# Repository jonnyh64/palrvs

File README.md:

# Rationale

This work started within the thread
"Project to create an ATX 80286 mainboard based on the IBM 5170"
at the Vintage Computer Federation Forums
(https://forum.vcfed.org/index.php?threads/project-to-create-an-atx-80286-mainboard-based-on-the-ibm-5170.1243108/).

The thread creator (username "rodney") looked for help on how to retrieve the PAL equations
of U87 and U130 on the IBM 5170 (the original IBM PC/AT computer) motherboard.
While I tried to help, he figured the equations out with other tooling from
http://techno-junk.org, but I found the topic interesting, so I kept on researching.

# History

Reverse engineering PAL chips has likely been done as early as in the 1980s, when plenty
of companies cloned the PC/AT. Probably this has just not been publicly documented.

The earliest description of the idea behind I could find was a schematic from 2007 with
title "PLD Analysis Board" developed by Charles M. (I'm trying to avoid publishing full names,
hence "M.") and apparently originally available at http://cgfm2.emuviews.com. This site
is no longer available, but a small subset of the information and schematics can be found at
http://techno-junk.org. A PCB design for these schematics is available at
https://github.com/pascalorama/paldumper.

Another description of the same idea has been published in the Vintage Computer Federation
Forums by user "Chuck(G)" (Blog entries "Cloning a PAL/HAL") in October 2011. He was describing
how to do the brute force readout on a PAL10L8 using a PC parallel port adapter and suggested
to use a microcontroller for more complicated PALs. The microcontroller idea was implemented
and described at https://electrickery.hosting.philpem.me.uk/digaud/arduino/ppread/palread.html.

In 2018, another implementation of the same idea was published at
https://github.com/psurply/ReGAL.

In 2020, https://github.com/DuPAL-PAL-DUmper was published, providing
support for more PALs (even registered ones).

The "Retro Chip Tester Professional" also supports reading protected PALs - see
https://8bit-museum.de/hardware-projekte/hardware-projekte-chip-tester-english/.

Rodney used the "EPROM readout adapter" from http://techno-junk.org which basically
"misuses" a chip programmer to apply all possible input combinations to the PAL via the
EPROM address lines A0..A17. An analysis tool is then used to transform the "EPROM dump"
into boolean equations. However, the boolean simplification and the job to produce a
"fuse map" JEDEC file used to burn the equations into a PAL/GAL device is left to other tools.

# Credits

Thanks go to:
- User "rodney" from the vcfed forums for kicking this all off
- User "Chuck(G)" from the vcfed forums for his excellent write-up on PAL reversing
- Charles M. from http://techno-junk.org for his "EPROM adapter" idea
- User "Eudimorphodon" from the vcfed forums for helping me understand PAL/GAL details

# Restrictions

The adapter and the scripts in this project only support the PAL16L8 chip for reading and
the GAL16V8 chip for writing. From the latter, only the subset of features necessary to use
it for replacing a PAL16L8 is used.

# Idea

The main idea of this project is to provide a "one stop solution" to make a clone
of a PAL16L8 in the form of a GAL16V8. It consists of:
- A KiCad project (including PCB) implementing http://techno-junk.org/files/adapter-v2-cap.png
- A Python script "pete.py" to convert a PAL "EPROM dump" into a truth table and GAL equations
- A Python script "simplegalasm.py" to convert GAL equations into a JED file which can be written into a GAL16V8

For complex PALs, it might be necessary to manually tune the GAL equations generated by "pete.py",
see examples below.

# Usage

## Build the adapter

You need to build up a circuit board according to the following schematic:

It is up to you to either hand wire this on a perfboard or to build it up with the
provided KiCad PCB. If you choose the latter, I have published it for easy ordering
at https://aisler.net/p/IUTCWVJK,
but you also might order it at your preferred PCB manufacturer, of course.

The original schematic from Charles M. suggested 4k7 resistors. This value doesn‘t work
for me (it does not give a stable reading with my minipro chip programmer) and neither
does 2k2. Only after going down to 1k, it worked for me and so you also might need to experiment.

## Install Python

Go to www.python.org, download a recent Python version (anything >= 3.7 should do) and install it.

## Generate "EPROM dump"

Put your PAL16L8 into the adapter and the adapter into your chip programmer.

(Do **NOT** put your PAL16L8 into your chip programmer directly - this will not work.)

Instruct your chip programming application to read a 27C020 EPROM and save the data
to a file, e.g. named pal.bin. The generated file length must be 262144
bytes. If your file length is different, something is broken. Do not try to continue,
it will not work.

E.g., if you own one of the popular MiniPRO TL866xx series of chip programmers and
have the excellent command line application from https://gitlab.com/DavidGriffith/minipro
installed, use:
```
minipro -p am27c020@dip32 -x -r pal.bin
```

**ATTENTION**: I found that this dump does not always work reliably, possibly due to timing
issues. Please make sure to perform the dump multiple times and compare the files. If you
cannot get multiple identical dumps, something is wrong in your setup.

## Generate the equations

On your command line, run `python3 pete.py pal.bin` (adapting the filename
to what you have chosen). This will generate a file called
pal_pete_equations.pld (adapted to your filename), which contains
the PAL equations.

## Fix up the equations

A GAL16V8 (like a PAL16L8) only supports up to 7 products per output value and
only up to 1 product per output enable. For complex PALs where one output value
depends on another output value, pete.py might not be able to find equations
within these limits. In this case, you need to think how to optimize further and
fix up the equations manually.

## Generate the JED file

On your command line, run `python3 simplegalasm.py pal_pete_equations.pld`
(again, adapting the filename to what you have chosen). This will generate a file called
pal.jed.

## Program your GAL

Put your GAL16V8B DIRECTLY into your chip programmer (NOT using the adapter!) and
instruct your EPROM programmer to write pal.jed to the GAL.

Again with the minipro command line utility as example:
```
minipro -p gal16v8b -w pal.jed
```

**ATTENTION**: Be careful to specify the exact GAL type you are using. "gal16v8" and
"gal16v8b" are **NOT** compatible at the chip programming level. The fuse maps (i.e.
the fuse numbers) are the same, but the order in which the fuse information is sent
during chip programming differ (this applies to fuse numbers 2120 to 2193). If
you specify the wrong type, programming seems to work fine, but the GAL outputs
will not behave according to the equations (just think about what happens when
you shuffle fuse numbers 2120 to 2193...).

# Examples

## Example 1

The first example analyzes the equations of U87 on the IBM 5170 (the original
IBM PC/AT computer) motherboard.

First, dump the PAL with the adapter PCB as described above:
```
minipro -p am27c020@dip32 -x -r ibm_5170_u87.bin
```

Then, let pete.py find out the equations:
As the U87 pin names are known from the IBM Personal Computer AT technical reference,
we pass them to pete.py:
```
python3 pete.py -p "RAS,MEMW,IOR,AIOW,Q1,IO_CS_16,AEN_1,AEN_2,Q4,FSYS_16,END_CYC,RES_0WS,DMA_AEN,XA0,XBHE,GATE_245,DIR_245,DATA_CONV" ibm_5170_u87.bin
```

The generated equations in ibm_5170_u87_pete_equations.pld will have one equation
which cannot be translated directly into a GAL fuse map. Let's leave
ibm_5170_u87_pete_equations.pld untouched and create a copy to modify:
```
cp ibm_5170_u87_pete_equations.pld ibm_5170_u87.pld
```

The problematic equation is:
```
XBHE.oe = !AEN_1
  # !AEN_2;
```

GAL16V8s only support one term per output enable. So we need to find a simplification.
Looking around in the remaining file, we will find:
```
!DMA_AEN = !AEN_1
  # !AEN_2;
```

That means, that the pin value equation (which **DOES** support more than one term!) for
`!DMA_AEN` is the same as for `XBHE.oe`. We can therefore replace the equation for `XBHE.oe`
like this:
```
XBHE.oe = !DMA_AEN;
```

Doing this change in ibm_5170_u87.pld gives as equations usable for creating the fuse map:
```
python3 simplegalasm.py ibm_5170_u87.pld
```

Congratulations, you can now program a GAL16V8B for replacing U87 in your IBM 5170 motherboard:
```
minipro -p gal16v8b -w ibm_5170_u87.jed
```

## Example 2

The second example analyzes the other PAL on the IBM 5170 motherboard: U130.

Get the EPROM dump using the adapter PCB:
```
minipro -p am27c020@dip32 -x -r ibm_5170_u130.bin
```

Let pete.py find out the equations:
```
python3 pete.py -p "RESET,ERROR,BUSY,XA0,XA3,XIOW,SM_IO,CS287,INTA,TIEDGND_11,NPCS,UNUSED_13,UNUSED_14,UNUSED_15,UNUSED_16,RESET_287,IRQ_13,BUSY_286" ibm_5170_u130.bin
```

This time, the equation for one output value will not be directly usable, so create a copy to modify again:
```
cp ibm_5170_u130_pete_equations.pld ibm_5170_u130.pld
```

The problematic equation is:
```
!UNUSED_14 = !RESET & XA3
  # !RESET & XIOW
  # !RESET & SM_IO
  # !RESET & CS287
  # !RESET & !INTA
  # ERROR
  # BUSY
  # TIEDGND_11;
```

GAL16V8s only support at most 7 terms per output value. So we need to find a simplification.
Looking around in the remaining file, we will find:
```
!IRQ_13 = ERROR
  # BUSY;
```

So, `ERROR # BUSY` can be replaced by `!IRQ_13`:
```
!UNUSED_14 = !RESET & XA3
  # !RESET & XIOW
  # !RESET & SM_IO
  # !RESET & CS287
  # !RESET & !INTA
  # !IRQ_13
  # TIEDGND_11;
```

Doing this change in ibm_5170_u130.pld gives as equations usable for creating the fuse map:
```
python3 simplegalasm.py ibm_5170_u130.pld
```

Congratulations, you can now program a GAL16V8B for replacing U130 in your IBM 5170 motherboard:
```
minipro -p gal16v8b -w ibm_5170_u130.jed
```

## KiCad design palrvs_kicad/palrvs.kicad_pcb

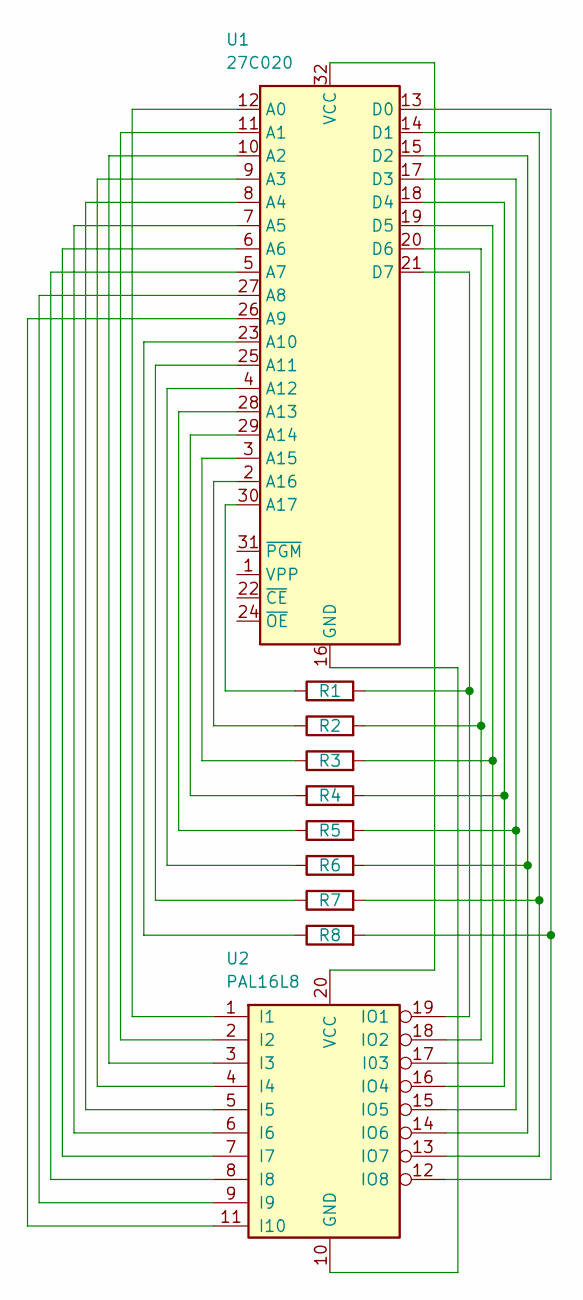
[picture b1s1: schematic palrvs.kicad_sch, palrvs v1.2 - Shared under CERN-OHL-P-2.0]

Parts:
R1, R2, R3, R4, R5, R6, R7, R8: 4k7; R_Axial_DIN0207_L6.3mm_D2.5mm_P7.62mm_Horizontal
U1: 27C020; Mirrored_DIP-32_W15.24mm
U2: PAL16L8; ZIF-20_W7.62mm_Socket

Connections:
unnamed: U1.12 (A0), U2.1 (I1)
unnamed: U1.11 (A1), U2.2 (I2)
unnamed: U1.10 (A2), U2.3 (I3)
unnamed: U1.9 (A3), U2.4 (I4)
unnamed: U1.8 (A4), U2.5 (I5)
unnamed: U1.7 (A5), U2.6 (I6)
unnamed: U1.6 (A6), U2.7 (I7)
unnamed: U1.5 (A7), U2.8 (I8)
unnamed: U1.27 (A8), U2.9 (I9)
unnamed: U1.26 (A9), U2.11 (I10)
unnamed: R8.1, U1.23 (A10)
unnamed: R7.1, U1.25 (A11)
unnamed: R6.1, U1.4 (A12)
unnamed: R5.1, U1.28 (A13)
unnamed: R4.1, U1.29 (A14)
unnamed: R3.1, U1.3 (A15)
unnamed: R2.1, U1.2 (A16)
unnamed: R1.1, U1.30 (A17)
unnamed: R8.2, U1.13 (D0), U2.12 (IO8)
unnamed: R7.2, U1.14 (D1), U2.13 (IO7)
unnamed: R6.2, U1.15 (D2), U2.14 (IO6)
unnamed: R5.2, U1.17 (D3), U2.15 (IO5)
unnamed: R4.2, U1.18 (D4), U2.16 (IO4)
unnamed: R3.2, U1.19 (D5), U2.17 (I03)
unnamed: R2.2, U1.20 (D6), U2.18 (IO2)
unnamed: R1.2, U1.21 (D7), U2.19 (IO1)
unnamed: U1.16 (GND), U2.10 (GND)
unnamed: U1.32 (VCC), U2.20 (VCC)

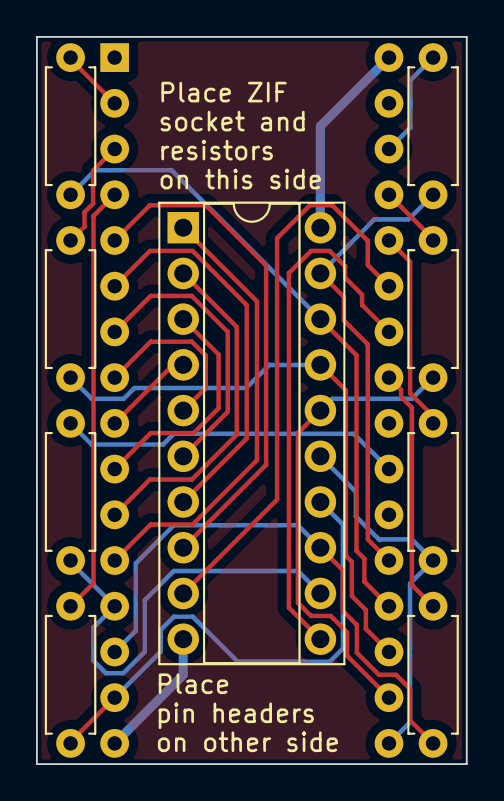
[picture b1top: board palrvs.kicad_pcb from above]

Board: 2 copper layers, 23.9 x 40.4 mm, 10 parts (1 on the bottom side), 28 nets.

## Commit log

2024-05-12 Initial commit of README
2024-05-12 Add pictures
2024-05-12 Refer to correct picture
2024-05-12 Initial commit of scripts
2024-05-12 Initial commit of KiCad files
2024-05-12 Initial commit of KiCad footprints
2024-12-22 Create LICENSE
2024-12-22 Mention "Retro Chip Tester Professional"
2025-04-23 Use my own boolean expression simplifier instead of depending on sympy
2025-04-23 Remove "SymPy" from README
2025-04-23 Re-add reference to "Retro Chip Tester Professional" which was accidentally removed
2025-04-23 Adapt README to change in equation term ordering
